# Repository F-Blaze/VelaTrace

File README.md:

# VelaTrace

**Catch small PCB mistakes before you order. A free KiCad 10 plugin.**

[-314cb0)](https://www.kicad.org/)

<p align="center"><sub>Recorded on the demo board in <a href="examples/velatrace-demo">examples/velatrace-demo</a>, which has deliberately planted issues. Waiting time is cut; the route took about 10 seconds.</sub></p>

## Why I built this

I ordered boards with mistakes I had missed. Each one cost me a re-order.

So I made a button. Click **Check design** and in about a second you get a short list of things to look at, with the evidence and a suggested fix. It only reads your board. No account, no key, no network.

## What it has found

- On one open-source board: **48 capacitors** labelled "10u" that all carried the part number of a **1 µF** part.
- On another: **7 resistors** of different values sharing **one 1 k part number**.

The second kind of find needs the optional JLCPCB parts list. I have tried it on three boards so far.

## What it checks

- LEDs with no series resistor.
- I2C pull-up problems.
- Duplicated chips, 0 Ω shorts, unset values.
- Power and polarity: missing regulator, VCAP and bootstrap capacitors, reversed LEDs and capacitors, MOSFET wiring, divider voltages, LDO dropout, rail-name mismatches, unprotected power connectors.
- MCU and USB: strap/boot pins, crystal load capacitors, swapped D+/D−, missing USB-C CC resistors, two outputs driving one net.
- Footprint fit: pad count, pitch, pin order and mounting type checked against the part number (optional lookup).
- Messy part values (`100n` vs `0.1uF` vs `100nF`).
- Wrong or out-of-stock JLCPCB part numbers (optional parts list).
- Early high-speed checks (beta): timing differences between paired lines and missing return paths, shown as notes. Full-speed USB (12 Mbit/s) is no longer held to high-speed rules.

Some checks are marked **experimental**; they show as Info notes, and **Setup > Hide experimental checks** hides them.

Full list: [docs/behavior-and-limits.md](docs/behavior-and-limits.md#built-in-audit-checks). You can also save a shareable offline report: [docs/report.md](docs/report.md).

## Install in 3 steps

You need KiCad 10 (tested on Windows only).

1. In KiCad open the **Plugin and Content Manager**, search for **VelaTrace**, click **Install**, then **Apply Pending Changes**. Without the Plugin Manager (offline, or an older KiCad index), download `VelaTrace-v0.1.0-alpha.3-pcm.zip` from the [v0.1.0-alpha.3 release](https://github.com/F-Blaze/VelaTrace/releases/tag/v0.1.0-alpha.3) and use **Install from File...**. (If you installed earlier with `git clone`, delete that `plugins/VelaTrace` folder first.)
2. When KiCad asks to enable the KiCad API, click **Yes**. (Missed it? **Preferences > Plugins**, tick **Enable KiCad API**.)
3. Open the PCB Editor. The first start installs about 300 MB of Python packages (about 4 minutes for me), then a VelaTrace button appears. Click it, then **Check design**.

No button? **Preferences > Plugins**, right-click VelaTrace, **Recreate Plugin Environment**. More help: [docs/install.md](docs/install.md).

## Try it safely

Open the demo board in [examples/velatrace-demo](examples/velatrace-demo) (also on the release page as `velatrace-demo-v0.1.0-alpha.3.zip`). It has mistakes planted on purpose. The check only reads your board, so nothing changes.

## Routing (optional)

VelaTrace also has its own router, **Vela-routing**, for small boards. Click **Route board** and you get a preview on the board, then KiCad's design check (DRC) runs on it. If you like it, click **Approve** and the copper is added in one step. One **Undo** takes it back.

How it did on 13 test boards: its routes passed KiCad's check in 20 of 39 runs, against 8 of 33 for Freerouting. 5 of those Freerouting misses were the plugin stopping the board before Freerouting ran. This is one small test set on one PC, so treat it as a hint. How it works and what was measured: [docs/VELA_ROUTING.md](docs/VELA_ROUTING.md).

Before routing, see [Details](#details) for the few settings it needs. Try it on a disposable copy first.

## Honest limits

- It is an **alpha**. Expect rough edges.
- **KiCad 10 only**, and **tested on Windows only**.
- It is a first pass, not a design review. On an earlier test of 12 boards it had never seen, **14 of 22** findings were right (64%); a later test on 10 more boards scored much lower (see [Details](#details)). **This version (alpha.3) has not yet been measured on boards it has never seen.** It won't catch every problem a reviewer would. The judges were AI reviewers, not human engineers, and the samples are small.
- In those tests it found only about **3 to 4 in 10** of the problems the reviewers found. Treat every result as a hint.
- I built it with AI help. That is exactly why I measured it. Numbers and method: [Details](#details).

## Feedback

Found a wrong or missing finding? Please file an [audit false positive](https://github.com/F-Blaze/VelaTrace/issues/new?template=audit_false_positive.yml) report. Bugs and ideas are welcome too.

## Privacy

Offline by default. Anything that uses the network is opt-in and listed in [docs/privacy.md](docs/privacy.md).

## Other tools worth a look

- [KiCadRoutingTools](https://github.com/drandyhaas/KiCadRoutingTools): its own router, differential pairs, length matching, BGA/QFN fanout.
- [kicad-happy](https://github.com/aklofas/kicad-happy): datasheet-aware design review.
- [kicad-jlcpcb-tools](https://github.com/Bouni/kicad-jlcpcb-tools): a mature JLCPCB workflow. VelaTrace's JLCPCB part is newer and narrower.

## Contributing

Contributions, forks and bug reports are welcome. Start with [CONTRIBUTING.md](CONTRIBUTING.md) and the [good first issues](https://github.com/F-Blaze/VelaTrace/labels/good%20first%20issue). Security reports: [SECURITY.md](SECURITY.md). I maintain this alone, with no response-time guarantee.

## License

[MIT](LICENSE), including Vela-routing. **Route board** no longer runs Freerouting (GPLv3). The old Freerouting adapter and its MIT launcher `WarmRouter.java` stay in the repo for research benchmarks only and load a separately downloaded, unmodified Freerouting JAR. Whether the two form a combined work is an open question I am reviewing; this README makes no legal claim either way.

The optional JLCPCB data files carry no licence statement, and the live lookup uses an undocumented JLCPCB website endpoint. See [docs/jlcpcb.md](docs/jlcpcb.md) and [docs/bom.md](docs/bom.md).

## Details

**More docs:** [UI guide](docs/ui.md), [behavior and limits](docs/behavior-and-limits.md), [write safety](docs/write-safety.md), [JLCPCB parts](docs/jlcpcb.md), [BOM tidy-ups](docs/bom.md).

**Before routing.** Save the board and project once. Enable the **User.9** layer for previews. Set every KiCad DRC check to at least *Warning* (VelaTrace refuses to route while any is *Ignore*; KiCad's defaults ignore five). Routing needs a `kicad-cli` that matches the running editor exactly, patch version included; if it is not found, enter its path in **Setup**. It routes only placed, unrouted boards (one track width and clearance for all nets, no differential pairs, no BGA fanout) and refuses anything else. Dense boards often end as a partial route you can reject. **Approve anyway** applies a route that failed DRC, after a confirmation. DRC-clean does not mean electrically correct. Steps: [docs/install.md](docs/install.md).

**Optional AI explanations.** Bring your own key (Gemini or any OpenAI-compatible endpoint) in **Setup**. Token counts and a hard call budget are shown first; the key stays in memory. Setup values: [docs/install.md](docs/install.md).

**How accuracy was measured.** The reviewers and the judge were AI agents (Claude Opus), not human experts. First test: on 12 open-source boards it had never seen, 44% of findings were judged correct (27% if unjudged findings count as wrong); I decided 5 borderline cases. I then fixed the rules that caused the wrong findings. Second test: 12 new public boards, answer key from 4 AI reviewers who did not see VelaTrace's output, written before scoring. 10 of the 13 findings they agreed on were correct (77%), 12 more were disputed and left out (as in the first test), and it found 38% of the problems they found. The fixes changed no finding on those new boards, so v0.1.0-alpha.2 scores the same there. Third test: 12 more public boards, answer key from 4 AI reviewers locked before the run; this time every finding outside the answer key was ruled by a separate AI reviewer instead of being left out. 14 of 22 findings were correct (64%) and it found 4 of 14 problems (29%); the version before the latest fixes scored 11 of 19 (58%) on the same boards. Four rules that were wrong too often (`decoupling.missing`, `i2c.pullup.missing`, `net.single_pin`, `pin.input_floating`) show as Info notes only. Fourth test (on the code just after alpha.2): 10 more public boards, same method. Only 17 of 82 findings were correct (21%); most of the rest were Info notes about labelled but unused connector pins on one board. Without those notes, 17 of 26 (65%). Alpha.3 fixes the causes found there, but it has not been re-measured on new boards yet, so no accuracy figure is claimed for it.

**JLCPCB parts list.** Opt-in download of about 181 MB (800 MB on disk), from the public data of the kicad-jlcpcb-tools project. It gives an offline table with tier, stock and price, flags mismatched LCSC numbers, writes the LCSC field to the board in one undoable step, and exports JLCPCB BOM, placement and Gerber files. It cannot edit the schematic (a KiCad 10 limit).

**Tested on** KiCad 10.0.4 and 10.0.6 on Windows. Linux and macOS are untested. To run the UI on fake data: `pip install -e '.[dev]'` then `python -m velatrace --demo`. Tests: `python -m pytest` (no key or KiCad needed).

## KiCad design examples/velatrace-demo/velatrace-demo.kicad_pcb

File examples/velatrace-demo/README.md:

# VelaTrace demo board

A small, purpose-made KiCad 10 project for demonstrating [VelaTrace](https://github.com/F-Blaze/VelaTrace)
(offline design audit, BOM savings, one-click Freerouting with preview / DRC / approve).

**This is a demo, not a product. It contains deliberately planted design mistakes. Do not manufacture it.**

## The board

USB-C powered I2C temperature + RTC node, 2 layers, 50 x 35 mm, 23 parts, unrouted (no tracks, no zones).
Only stock KiCad library symbols and footprints (0603 passives, SOT-23, SOIC-8, SOD-123, through-hole connectors).

| Block | Parts |
|---|---|
| USB-C power input (power only, 5.1k on CC1/CC2, series Schottky) | J1, R1, R2, D3 |
| 3.3 V LDO (MCP1700) and output capacitor | U1, C1 |
| Power LED | D1 |
| LM75B I2C temperature sensor, alert pull-up | U3, C3, R7 |
| DS3231MZ I2C real-time clock, 1 Hz LED on SQW, backup battery connector (JST PH) | U4, C4, C5, R8, D2, J3 |
| I2C pull-ups (two sets) | R3, R4, R5, R6 |
| I2C header (GND, 3V3, SDA, SCL, ALERT) | J2 |
| Test points (GND, 3V3) | TP1, TP2 |

Files: `velatrace-demo.kicad_pro`, `velatrace-demo.kicad_sch`, `velatrace-demo.kicad_pcb`.

## Planted issues (what the audit should find)

| # | Planted mistake | VelaTrace rule | Shown as |
|---|---|---|---|
| 1 | Power LED D1 sits straight across +3V3 / GND with no series resistor | `led.no_resistor` | Error |
| 2 | LED D2 still has the symbol default value "LED" | `value.missing` | Warning |
| 3 | SDA and SCL each have two pull-ups (R3 + R5, R4 + R6) | `i2c.pullup.redundant` (x2) | Saving |
| 4 | The same capacitor is written "100n" (C4, C5) and "0.1uF" (C3) | `bom.value_normalise` | Saving |
| 5 | Alert pull-up R7 is 4.7k while 5.1k (R1, R2) is already on the BOM | `bom.value_merge` | Saving |
| 6 | Battery connector J3 feeds VBAT with no reverse-polarity / ESD part | `connector.power_unprotected` | Note |
| 7 | LDO U1 has no input capacitor on +5V | `decoupling.missing` (beta rule) | Note |

Everything else is meant to be clean: 8 findings in total, nothing unplanned.

## Notes for recording

- All DRC checks are enabled in the project (VelaTrace refuses to route while any check is set to "ignore"),
  and the User.9 layer is enabled (VelaTrace draws its routing preview there).
- Net class Default: 0.2 mm track, 0.2 mm clearance, 0.6 / 0.3 mm via.
- The unrouted board has no DRC errors other than the expected unconnected items.
- Freerouting 2.1.0 routes it 100 % in roughly 10-20 s, normally with zero or one via.

## License

MIT

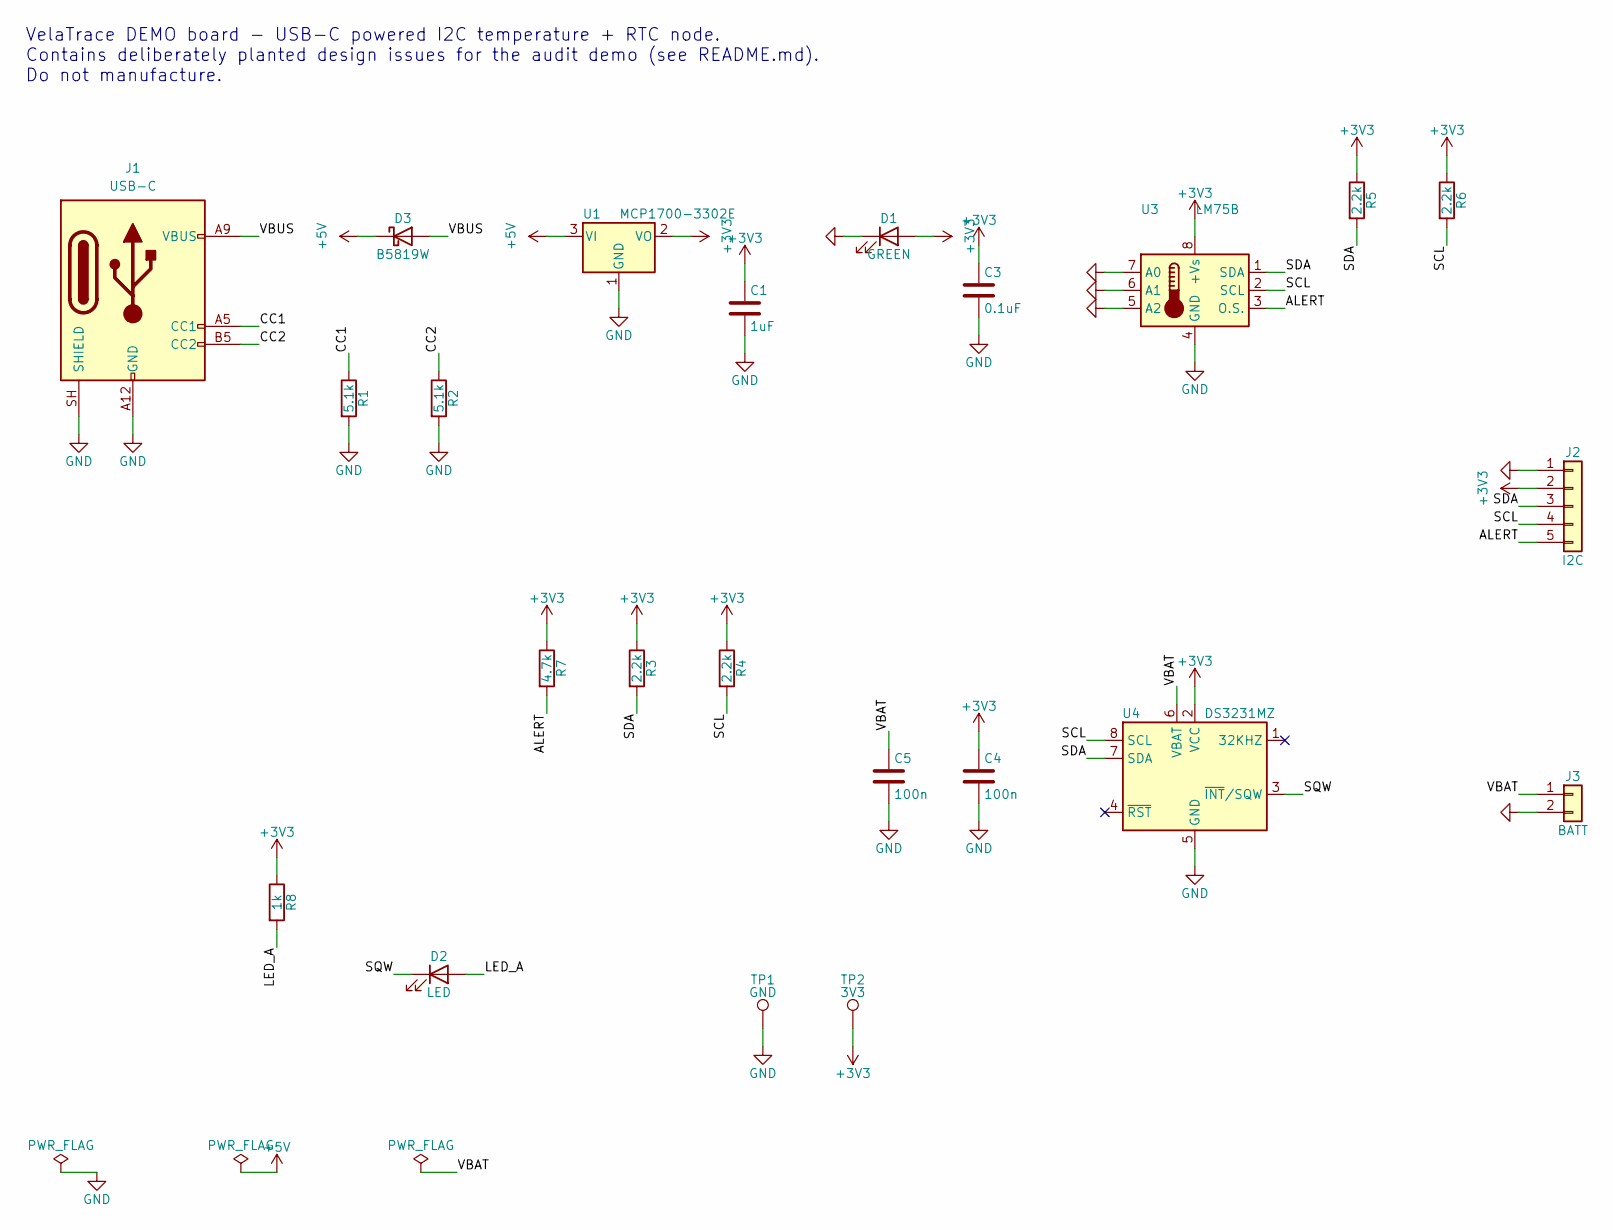
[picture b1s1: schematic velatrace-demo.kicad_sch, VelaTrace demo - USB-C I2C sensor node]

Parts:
C1: 1uF; C_0603_1608Metric
C3: 0.1uF; C_0603_1608Metric
C4, C5: 100n; C_0603_1608Metric
D1: GREEN; LED_0603_1608Metric
D2: LED; LED_0603_1608Metric
D3: B5819W; D_SOD-123
J1: USB-C; USB_C_Receptacle_GCT_USB4125-xx-x_6P_TopMnt_Horizontal
J2: I2C; PinHeader_1x05_P2.54mm_Vertical
J3: BATT; JST_PH_B2B-PH-K_1x02_P2.00mm_Vertical
R1, R2: 5.1k; R_0603_1608Metric
R3, R4, R5, R6: 2.2k; R_0603_1608Metric
R7: 4.7k; R_0603_1608Metric
R8: 1k; R_0603_1608Metric
TP1: GND; TestPoint_THTPad_D1.5mm_Drill0.7mm
TP2: 3V3; TestPoint_THTPad_D1.5mm_Drill0.7mm
U1: MCP1700-3302E; SOT-23
U3: LM75B; SOIC-8_3.9x4.9mm_P1.27mm
U4: DS3231MZ; SOIC-8_3.9x4.9mm_P1.27mm

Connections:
+3V3: C1.1, C3.1, C4.1, D1.2 (A), J2.2, R3.1, R4.1, R5.1, R6.1, R7.1, R8.1, TP2.1 (1_1), U1.2 (VO), U3.8 (+Vs), U4.2 (VCC)
+5V: D3.1 (K), U1.3 (VI)
/ALERT: J2.5, R7.2, U3.3 (O.S.)
/CC1: J1.A5 (CC1), R1.1
/CC2: J1.B5 (CC2), R2.1
/LED_A: D2.2 (A), R8.2
/SCL: J2.4, R4.2, R6.2, U3.2 (SCL), U4.8 (SCL)
/SDA: J2.3, R3.2, R5.2, U3.1 (SDA), U4.7 (SDA)
/SQW: D2.1 (K), U4.3 (~INT/SQW)
/VBAT: C5.1, J3.1, U4.6 (VBAT)
/VBUS: D3.2 (A), J1.A9 (VBUS), J1.B9 (VBUS)
GND: C1.2, C3.2, C4.2, C5.2, D1.1 (K), J1.A12 (GND), J1.B12 (GND), J1.SH (SHIELD), J2.1, J3.2, R1.2, R2.2, TP1.1 (1_1), U1.1 (GND), U3.4 (GND), U3.5 (A2), U3.6 (A1), U3.7 (A0), U4.5 (GND)

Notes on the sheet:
VelaTrace DEMO board - USB-C powered I2C temperature + RTC node. Contains deliberately planted design issues for the audit demo (see README.md). Do not manufacture.

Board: 2 copper layers, 23 parts (0 on the bottom side), 12 nets, no tracks yet.

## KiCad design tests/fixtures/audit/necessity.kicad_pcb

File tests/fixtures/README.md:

# Test fixtures

These small, self-contained fixtures were authored for VelaTrace and are covered by the repository's MIT license. They contain no third-party library footprints. `routing/freerouting-2.1.0-duplicate-stubs.ses` is router output from the maintainer's own practice board, published with their permission.

- `audit/necessity.kicad_pcb` is a placed, unrouted two-layer board with an outline and embedded footprint geometry. `necessity.kicad_pro` supplies matching project rules; `necessity.xml` independently records the same pin-to-net connectivity.
- C1 is bulk capacitance and C2 is local decoupling on the same VCC/GND rail; they must not be flagged as duplicates.
- U1 and U2 are identical nearby temperature sensors with identical pin-to-net mappings and a confirmed shared role; U2 must be flagged as a duplicate suggestion. With only the XML netlist, missing placement downgrades this to possible redundancy.
- The audit PCB is intentionally unrouted. Unconnected items are expected; it is not a DRC-clean manufacturing reference. The test-only position join verifies XML/PCB agreement, not the production IPC reader.
- `routing/simple.dsn` is a minimal authored routing input. `routing/freerouting-2.1.0.ses` is actual external Freerouting output for that fixture. The native test runs the router again instead of relying solely on a canned SES result.
- `routing/freerouting-2.1.0-duplicate-stubs.ses` is actual Freerouting 2.1.0 output for the VelaTrace practice board (J1, U1, R1, C1; nets VIN/GND/VOUT). It intermittently repeats pad-escape stubs in both directions on both copper layers; the regression requires them to be dropped once when the SES is parsed.

The audit PCB and project were parsed and checked by the real official KiCad 10.0.6 CLI on 2026-09-22. The regression confirms nonzero DRC/unconnected counts and refusal when a rule check is disabled. Live editor undo remains a separate release check.

Opening a fixture in KiCad and saving it may rewrite its formatting. Use a copy for interactive release checks.

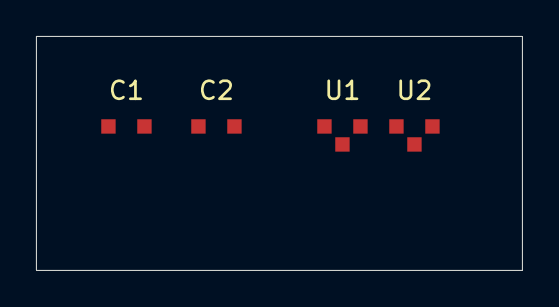
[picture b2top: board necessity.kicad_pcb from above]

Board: 2 copper layers, 27.0 x 13.0 mm, 4 parts (0 on the bottom side), 3 nets, no tracks yet.

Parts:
C1: 100uF; Bulk_Capacitor
C2: 100nF; Decoupling_Capacitor
U1, U2: TEMP_SENSOR; Temperature_Sensor

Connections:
GND: C1.2, C2.2, U1.2, U2.2
TEMP: U1.3, U2.3
VCC: C1.1, C2.1, U1.1, U2.1
